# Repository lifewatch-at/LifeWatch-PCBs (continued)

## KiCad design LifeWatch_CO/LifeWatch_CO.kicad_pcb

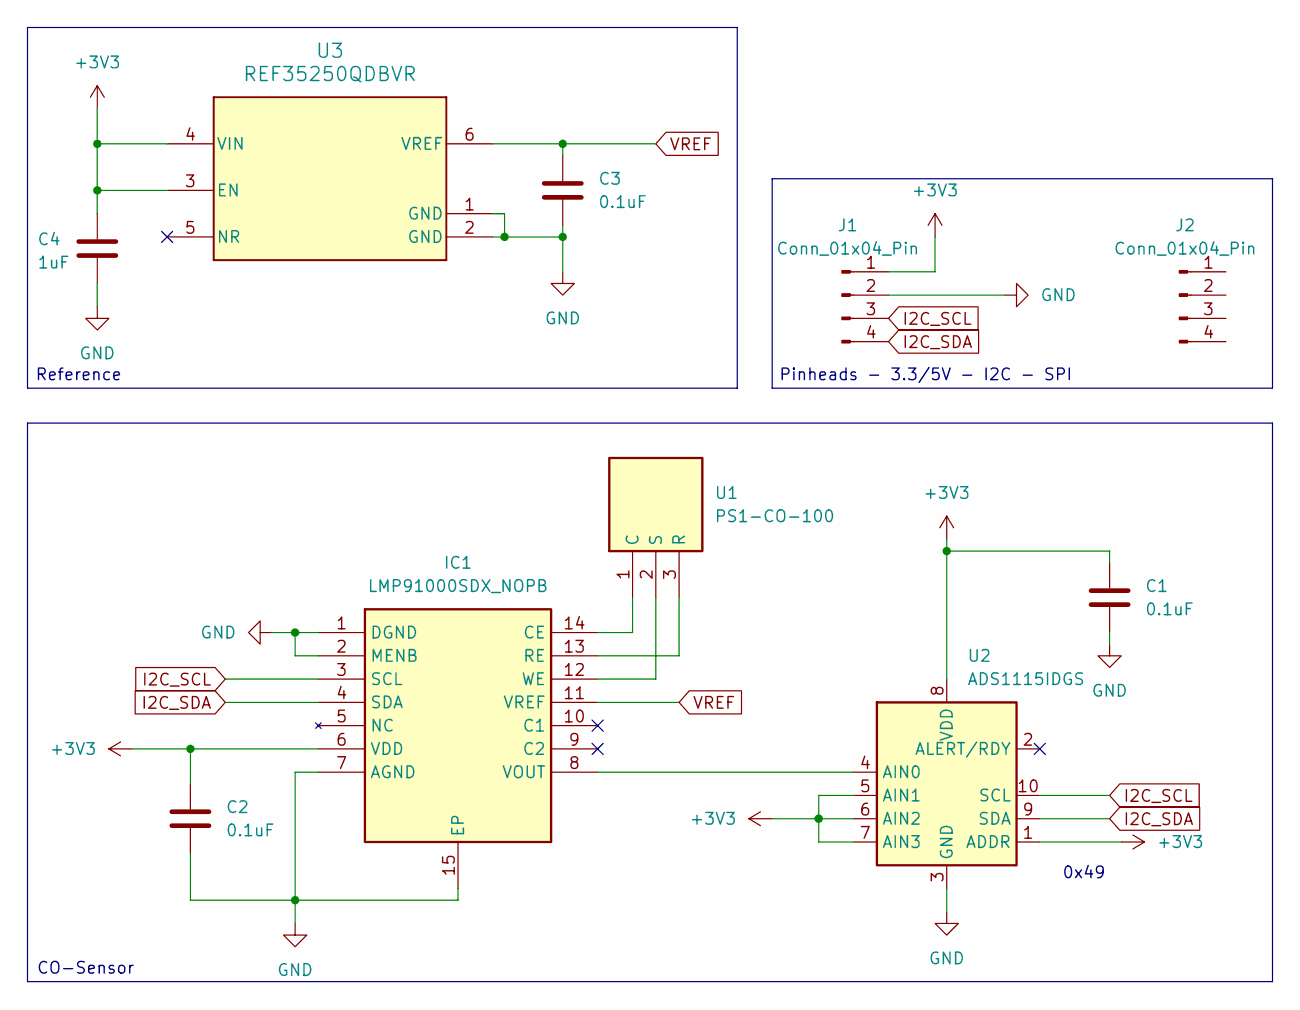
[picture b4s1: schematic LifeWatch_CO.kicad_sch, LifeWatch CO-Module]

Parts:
C1, C2, C3: 0.1uF; C_0402_1005Metric; Manufacturer_Part_Number CL05B104KP5NNNC
C4: 1uF; C_0603_1608Metric; Manufacturer_Part_Number CC0603KRX7R7BB105
IC1: LMP91000SDX_NOPB; WSON-14-1EP_4.0x4.0mm_P0.5mm_EP2.6x2.6mm; Mouser Part Number 926-LMP91000SDX/NOPB
J1, J2: Conn_01x04_Pin; PinHeader_1x04_P2.54mm_Vertical
U1: PS1-CO-100; PS1CO100; Mouser Part Number 523-PS1-CO-1000
U2: ADS1115IDGS; TSSOP-10_3x3mm_P0.5mm; Manufacturer_Part_Number ADS1115IDGSR
U3: REF35250QDBVR; DBV0006A-IPC_A; Manufacturer_Part_Number REF35250QDBVR

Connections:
+3V3: C1.1, C2.1, C4.1, IC1.6 (VDD), J1.1, U2.1 (ADDR), U2.5 (AIN1), U2.6 (AIN2), U2.7 (AIN3), U2.8 (VDD), U3.3 (EN), U3.4 (VIN)
GND: C1.2, C2.2, C3.2, C4.2, IC1.1 (DGND), IC1.2 (MENB), IC1.7 (AGND), IC1.15 (EP), J1.2, U2.3 (GND), U3.1 (GND), U3.2 (GND)
I2C_SCL: IC1.3 (SCL), J1.3, U2.10 (SCL)
I2C_SDA: IC1.4 (SDA), J1.4, U2.9 (SDA)
unnamed: IC1.14 (CE), U1.1 (C)
unnamed: IC1.13 (RE), U1.3 (R)
unnamed: IC1.8 (VOUT), U2.4 (AIN0)
unnamed: C3.1, IC1.11 (VREF), U3.6 (VREF)
unnamed: IC1.12 (WE), U1.2 (S)

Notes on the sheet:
Reference
0x49
Pinheads - 3.3/5V - I2C - SPI
CO-Sensor

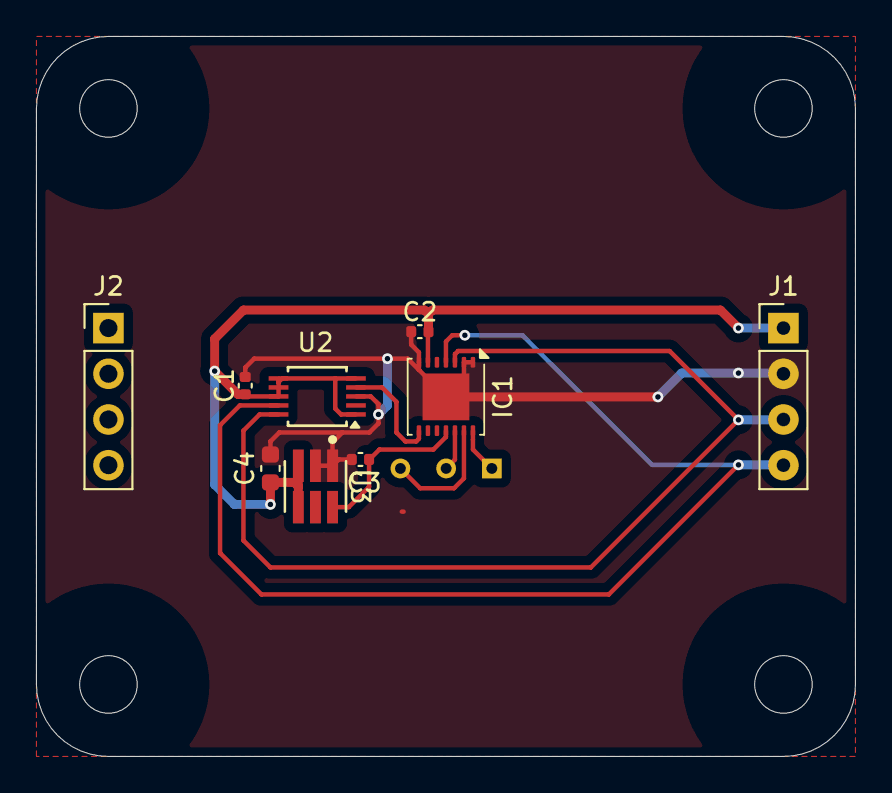
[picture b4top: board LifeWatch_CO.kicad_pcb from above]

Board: 2 copper layers, 45.5 x 40.0 mm, 10 parts (1 on the bottom side), 9 nets.

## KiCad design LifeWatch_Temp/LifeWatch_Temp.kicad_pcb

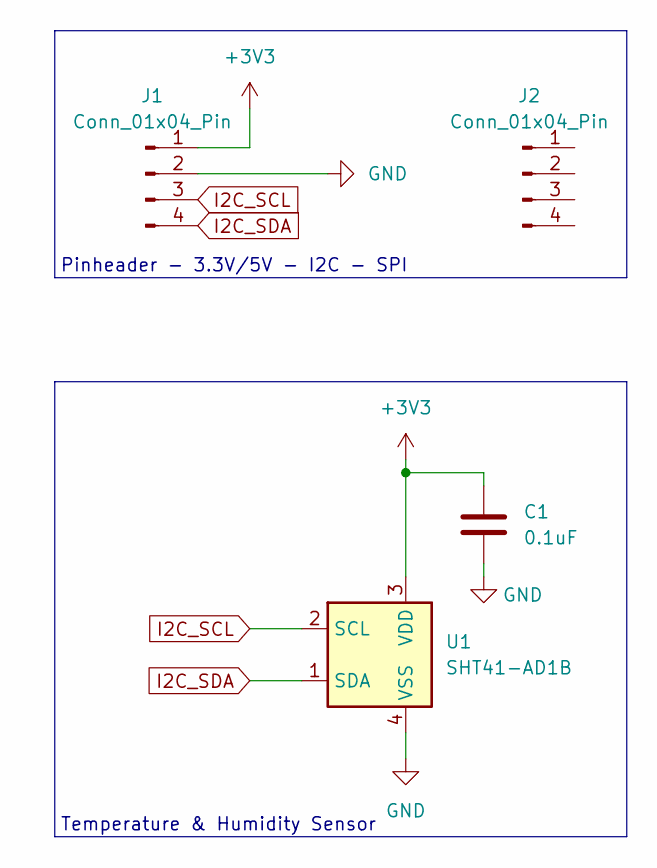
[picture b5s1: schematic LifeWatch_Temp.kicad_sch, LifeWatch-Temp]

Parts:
C1: 0.1uF; C_0402_1005Metric; Manufacturer_Part_Number CL05B104KP5NNNC
J1, J2: Conn_01x04_Pin; PinHeader_1x04_P2.54mm_Vertical
U1: SHT41-AD1B; Sensirion_DFN-4_1.5x1.5mm_P0.8mm_SHT4x_NoCentralPad; Manufacturer_Part_Number SHT41-AD1B

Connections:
+3V3: C1.1, J1.1, U1.3 (VDD)
GND: C1.2, J1.2, U1.4 (VSS)
I2C_SCL: J1.3, U1.2 (SCL)
I2C_SDA: J1.4, U1.1 (SDA)

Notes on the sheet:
Pinheader - 3.3V/5V - I2C - SPI
Temperature & Humidity Sensor

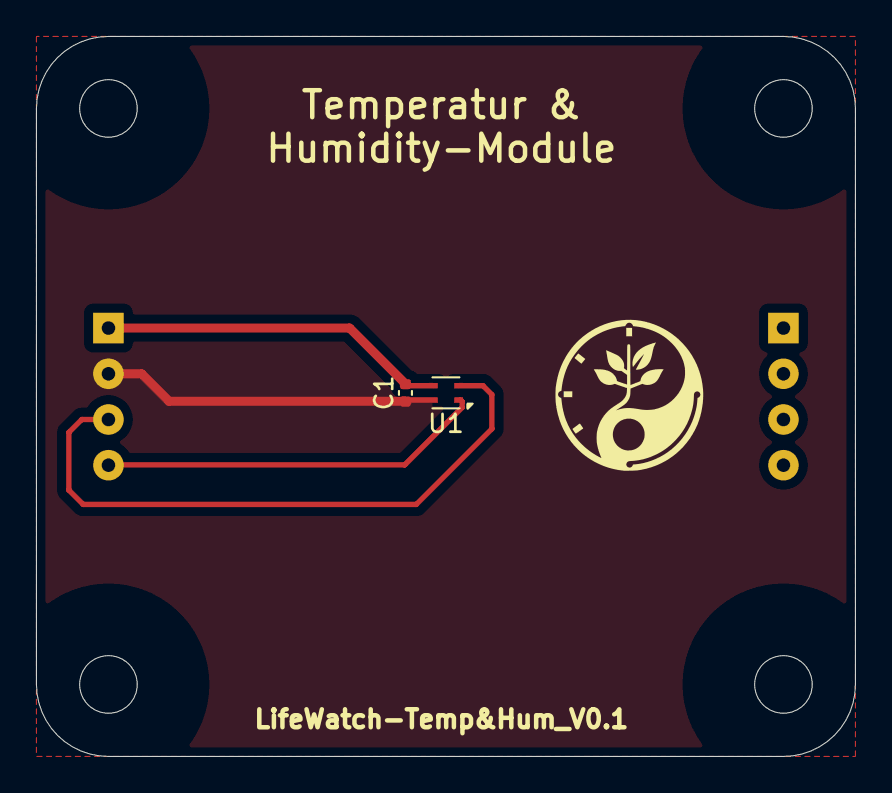
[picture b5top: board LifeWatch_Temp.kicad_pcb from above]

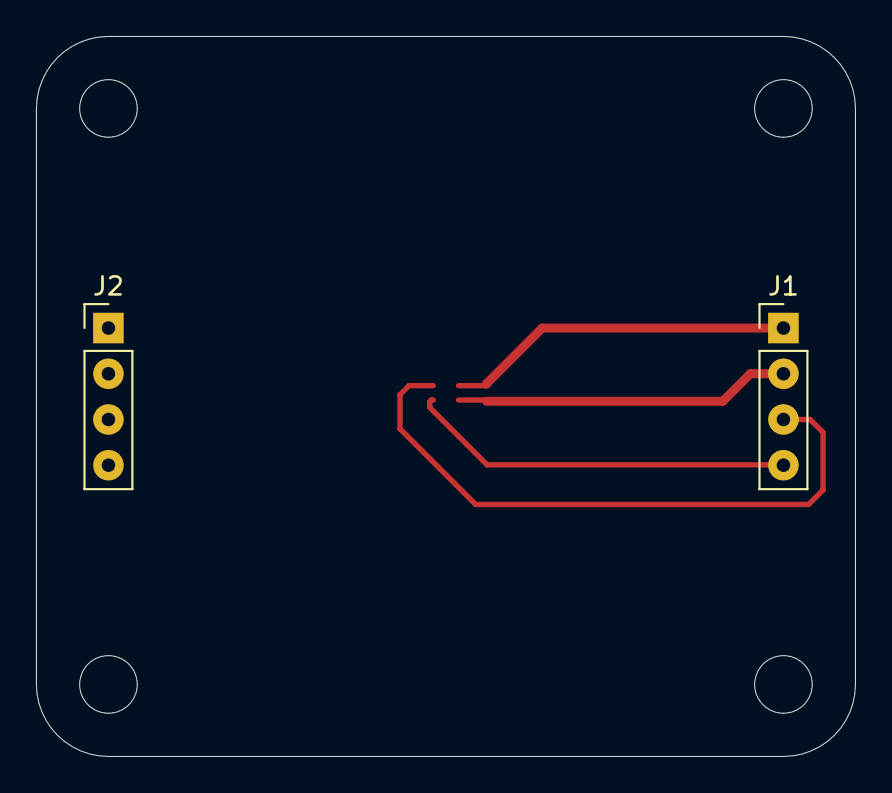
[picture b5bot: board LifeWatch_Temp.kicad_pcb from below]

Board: 2 copper layers, 45.5 x 40.0 mm, 4 parts (2 on the bottom side), 4 nets.

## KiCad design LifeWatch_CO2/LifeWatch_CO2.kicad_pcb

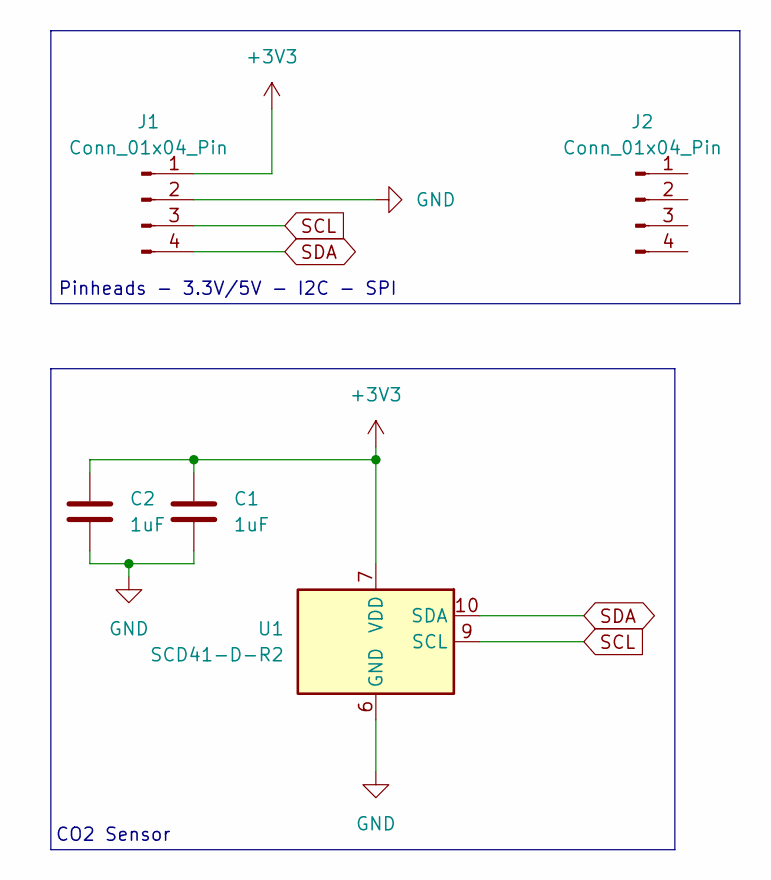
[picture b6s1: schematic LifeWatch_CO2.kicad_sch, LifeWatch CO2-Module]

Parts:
C1, C2: 1uF; C_0603_1608Metric; Manufacturer_Part_Name CC0603KRX7R7BB105
J1, J2: Conn_01x04_Pin; PinHeader_1x04_P2.54mm_Vertical
U1: SCD41-D-R2; Sensirion_SCD4x-1EP_10.1x10.1mm_P1.25mm_EP4.8x4.8mm; Manufacturer_Part_Name SCD-41

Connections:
+3V3: C1.1, C2.1, J1.1, U1.7 (VDD), U1.19 (VDD)
GND: C1.2, C2.2, J1.2, U1.6 (GND), U1.20 (GND), U1.21 (GND)
SCL: J1.3, U1.9 (SCL)
SDA: J1.4, U1.10 (SDA)

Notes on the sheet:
Pinheads - 3.3V/5V - I2C - SPI
CO2 Sensor

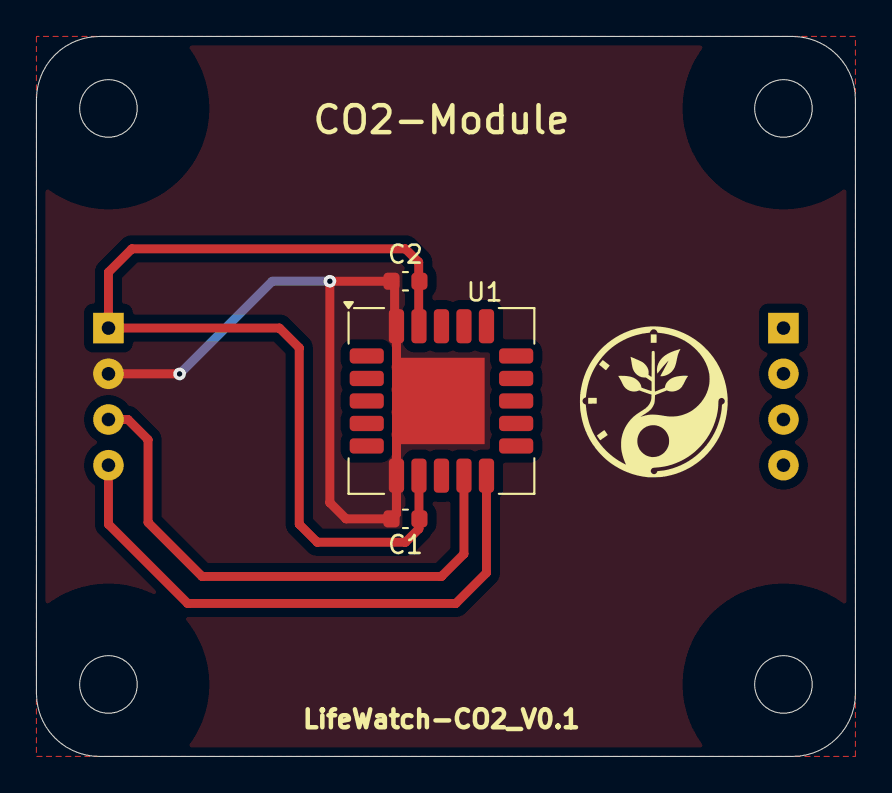
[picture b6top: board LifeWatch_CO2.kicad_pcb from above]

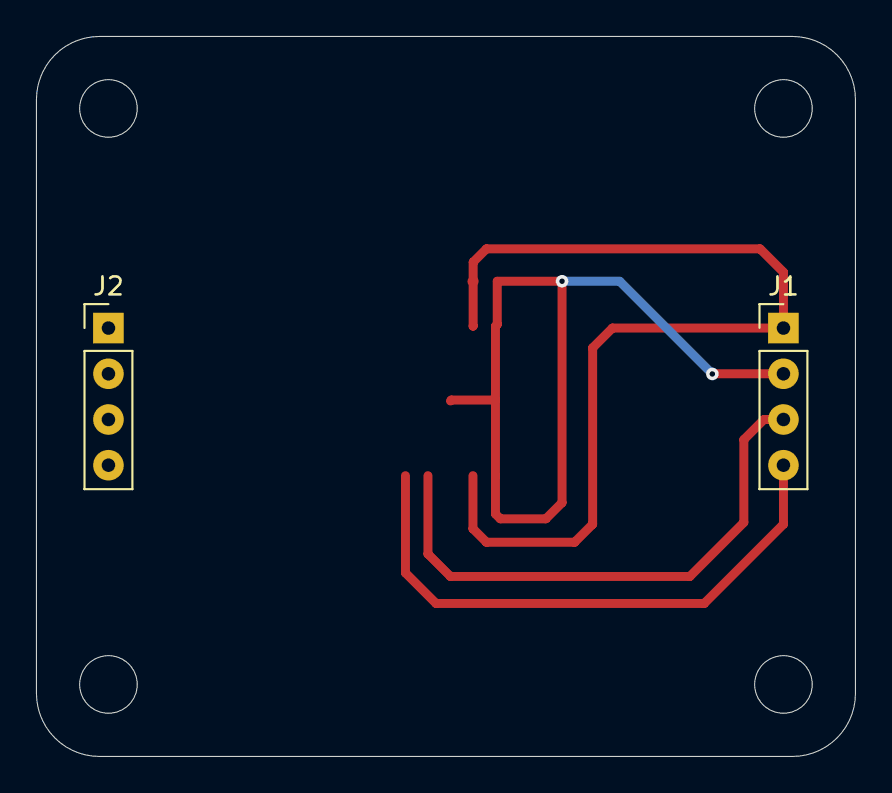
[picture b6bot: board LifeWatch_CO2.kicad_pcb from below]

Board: 2 copper layers, 45.5 x 40.0 mm, 5 parts (2 on the bottom side), 4 nets.

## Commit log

2025-07-20 init commit
